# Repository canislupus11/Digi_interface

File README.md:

<div align="center">
<br>

</div>

# Uniwersalny Interfejs Radiowy / Universal Radio Interface

> Kraków, 31 sierpnia 2026 | Hackerspace Kraków  
> Licencja / License: [CC BY-NC-SA](https://creativecommons.org/licenses/by-nc-sa/4.0/)

---

##  Polski (English below)

### Opis projektu

Uniwersalny interfejs radiowy to otwarto-sprzętowy projekt płytki PCB, której celem jest stworzenie jak najbardziej elastycznego interfejsu do **emisji cyfrowych** oraz **zdalnej kontroli urządzeń radiowych (TRX)**. Interfejs zaprojektowano z myślą o kompatybilności z możliwie największą liczbą modeli i producentów transceiverów.

### Główne założenia

- **Uniwersalność** – współpraca z szeroką gamą modeli TRX różnych producentów
- **Minimalizacja okablowania** – w skrajnym przypadku wystarczy kabel USB i kabel sygnałowy do radia
- **Pełna separacja galwaniczna** – izolacja zaraz za gniazdem USB chroni sprzęt przed przepięciami i biegającym RF

### Moduły

| # | Moduł | Chip |
|---|-------|------|
| 1 | HUB USB | **Fe1.1s** |
| 2 | Kodek dźwięku na USB (źródło dla emisji cyfrowych) | **CM108B** |
| 3 | 4-portowy konwerter USB → UART (CAT/CI-V, CW, PTT, FSK) | **CP2105** |
| 4 | Konwerter poziomów RS232/TTL | **MAX232** |
| 5 | Zasilacz (szeroki zakres napięć wejściowych: 7–18 V) | **AMS1117-5.0** |
| 6 | Moduł zworkologii – konfiguracja portów CAT, linii CW, PTT i FSK (w tym z konwerterem poziomów) | – |

### PCB

- Dwustronna płytka w technologii SMD
- Projekt wykonany w **KiCad 9** — pliki schematu, PCB oraz biblioteki footprintów i symboli dostępne w tym repozytorium
- Elementy mają przypisane identyfikatory JLCPCB, dzięki czemu można bezpośrednio zamówić płytkę z usługą montażu SMD (PCBA) — wystarczy wygenerować pliki Gerber, BOM i pliki pick & place z KiCad i wgrać je na stronę JLCPCB
- Katalog `bom/` zawiera interaktywny plik HTNL ułatwiający montaż

### Jak zacząć

1. Sklonuj lub pobierz repozytorium
2. Otwórz `interfejs_digi.kicad_pro` w KiCad 9
3. Przejrzyj schemat (`interfejs_digi.kicad_sch`) i projekt PCB (`interfejs_digi.kicad_pcb`)
4. Wygeneruj pliki Gerber, BOM oraz pick & place z poziomu KiCad
5. Wgraj pliki na stronę [JLCPCB](https://jlcpcb.com) i zamów płytkę z montażem SMD (PCBA) — identyfikatory elementów są już uzupełnione
6. Po otrzymaniu płytki skonfiguruj zworki zgodnie z używanym modelem TRX

### Pinout gniazd RJ45

Interfejs wyprowadza sygnały na dwóch gniazdach RJ45 (HX-RJ45 90 5631-1X1 8P8C).

**RJ1 — gniazdo główne**

| Pin | Sygnał | Opis |
|-----|--------|------|
| 1 | CAT1\_RX | CAT RX/CI-V (port 1) |
| 2 | CAT1\_TX | CAT TX (port 1) |
| 3 | GND\_IN | Masa zasilania |
| 4 | PWR\_IN | Zasilanie 7-18V (wejście) |
| 5 | PTT\_OUT | Wyjście PTT (otwarty dren, tranzystor 2N7002) |
| 6 | GND | Masa sygnałowa |
| 7 | AUDIO\_OUT | Wyjście audio do radia (TX) |
| 8 | AUDIO\_IN | Wejście audio z radia (RX) |

**RJ2 — gniazdo dodatkowe**

| Pin | Sygnał | Opis |
|-----|--------|------|
| 1 | CAT2\_RX | CAT RX (port 2) |
| 2 | CAT2\_TX | CAT TX (port 2) |
| 3 | FSK\_OUT | Wyjście FSK (otwarty dren, tranzystor 2N7002) |
| 4 | 5V_OUT | Wyjście 5V za stabilizatorem |
| 5 | CW\_OUT | Wyjście kluczowania CW (otwarty dren, tranzystor 2N7002) |
| 6 | – | Niepodłączony |
| 7 | – | Niepodłączony |
| 8 | – | Niepodłączony |

Wyjścia PTT, CW i FSK są wyjściami otwartego drenu przez tranzystor MOSFET 2N7002 z diodą LED sygnalizacyjną. Masa obu gniazd jest wspólna (pin 10 złącza RJ45 podłączony do GND).

### Konfiguracja zworkami

Zworki J7–J11 pozwalają elastycznie przypisać sygnały do linii sterujących oraz wybrać poziomy napięć. Każda zworka ma 6 pinów (3 pary), co umożliwia niezależny wybór dla każdej linii.

**J7, J8 — CAT\_1 i CAT\_2**

Pod każdym złączem CAT znajduje się goldpin 2×3 z dwiema klasycznymi zworkami — osobno dla linii RX i TX. Obie zworki ustawia się zawsze w tej samej pozycji. Konfiguracja jest wspólna dla CAT\_1 i CAT\_2:

| Pozycja zworek | Poziom sygnału |
|----------------|----------------|
| obie zworki **w górze** | TTL (5 V) |
| obie zworki **w dole** | RS232 (±12 V) |

**J9 — CW** — wybór źródła sygnału CW spośród linii UART:

| Pozycja zworki | Źródło |
|----------------|--------|
| piny 1–2 | DTR\_1 |
| piny 3–4 | RTS\_1 |
| piny 5–6 | RTS\_2 |

**J10 — PTT** — wybór źródła sygnału PTT:

| Pozycja zworki | Źródło |
|----------------|--------|
| piny 1–2 | DTR\_1 |
| piny 3–4 | RTS\_1 |
| piny 5–6 | RTS\_2 |

**J11 — FSK** — wybór źródła sygnału FSK:

| Pozycja zworki | Źródło |
|----------------|--------|
| piny 1–2 | DTR\_2 |
| piny 3–4 | RTS\_2 |
| piny 5–6 | RTS\_1 |

**J2 — CI-V** — gniazdo CI-V (Icom). Po włożeniu zworki sygnał CAT1\_TX\_TTL jest zwrotnie podłączony przez diodę D5 (1N5819WS) do CAT1\_RX\_TTL, realizując magistralę jednolinową wymaganą przez protokół CI-V.

**LDO\_BYPASS** — lutowana zworka (solder jumper) bypasująca stabilizator napięcia (AMS1117-5.0). Jeśli układ jest zasilany napięciem **5 V** zamiast standardowych 7–18 V (np. bezpośrednio z zasilacza 5 V przez gniazdo RJ1 pin 4), należy zewrzeć tę zworkę cyną, aby ominąć regulator LDO.

> **Ostrzeżenie:** Po zwarciu zworki LDO\_BYPASS stabilizator napięcia jest całkowicie pomijany. Napięcie zasilające trafia bezpośrednio na układ bez żadnej regulacji. Podanie napięcia wyższego niż 5 V przy zwartej zworce **może trwale uszkodzić układ**. Przed podaniem zasilania upewnij się, że źródło napięcia dostarcza dokładnie 5 V.

### Licencja

Projekt udostępniony na licencji **Creative Commons BY-NC-SA**. Możesz go swobodnie używać, modyfikować i udostępniać pod warunkiem podania autora, zachowania tej samej licencji i braku użytku komercyjnego.

---

##  English

### Project Description

The Universal Radio Interface is an open-hardware PCB project designed to provide a flexible interface for **digital mode operations** and **remote control of radio transceivers (TRX)**. The board is designed to be compatible with as many TRX models and manufacturers as possible.

### Design Goals

- **Universality** – works with a wide range of TRX models from various manufacturers
- **Minimal cabling** – in the simplest setup only a USB cable and radio signal cable needed
- **Full galvanic isolation** – isolation placed immediately after the USB connector protects equipment from voltage spikes and stray RF

### Modules

| # | Module | Chip |
|---|--------|------|
| 1 | USB Hub | **Fe1.1s** |
| 2 | USB Audio Codec (source for digital modes) | **CM108B** |
| 3 | 4-port USB → UART converter (CAT/CI-V, CW, PTT, FSK) | **CP2105** |
| 4 | RS232/TTL Level Converter | **MAX232** |
| 5 | Power Supply (wide input voltage range: 7–18 V) | **AMS1117-5.0** |
| 6 | Jumper configuration module – configures CAT ports, CW, PTT and FSK lines (including level converter options) | – |

### PCB

- Double-sided SMD board
- Designed in **KiCad 9** — schematic, PCB layout, footprint and symbol libraries all included in this repository
- All components have JLCPCB part IDs assigned, so the board can be ordered with SMD assembly (PCBA) — simply generate Gerber, BOM and pick & place files from KiCad and upload them to JLCPCB
- The `bom/` directory contains an interactive HTML file to assist with assembly.

### Getting Started

1. Clone or download this repository
2. Open `interfejs_digi.kicad_pro` in KiCad 9
3. Review the schematic (`interfejs_digi.kicad_sch`) and PCB layout (`interfejs_digi.kicad_pcb`)
4. Generate Gerber, BOM and pick & place files from KiCad
5. Upload the files to [JLCPCB](https://jlcpcb.com) and order the board with SMD assembly (PCBA) — component IDs are already filled in
6. Once the board arrives, configure the jumpers for your TRX model

### RJ45 Connector Pinout

The interface exposes signals on two RJ45 connectors (HX-RJ45 90 5631-1X1 8P8C). 

**RJ1 — Main connector**

| Pin | Signal | Description |
|-----|--------|-------------|
| 1 | CAT1\_RX | CAT/CI-V receive (port 1) |
| 2 | CAT1\_TX | CAT/CI-V transmit (port 1) |
| 3 | GND\_IN | Power ground |
| 4 | PWR\_IN | 7-18V power input |
| 5 | PTT\_OUT | PTT output (open drain, 2N7002 MOSFET) |
| 6 | GND | Signal ground |
| 7 | AUDIO\_OUT | Audio output to radio (TX) |
| 8 | AUDIO\_IN | Audio input from radio (RX) |

**RJ2 — Secondary connector**

| Pin | Signal | Description |
|-----|--------|-------------|
| 1 | CAT2\_RX | CAT receive (port 2) |
| 2 | CAT2\_TX | CAT transmit (port 2) |
| 3 | FSK\_OUT | FSK output (open drain, 2N7002 MOSFET) |
| 4 | 5V_OUT | 5V output, after LDO |
| 5 | CW\_OUT | CW keying output (open drain, 2N7002 MOSFET) |
| 6 | – | Not connected |
| 7 | – | Not connected |
| 8 | – | Not connected |

PTT, CW and FSK outputs are open-drain via 2N7002 MOSFET transistors, each with a status LED indicator. The ground of both connectors is shared (RJ45 pin 10 tied to GND).

### Jumper Configuration

Jumpers J7–J11 allow flexible assignment of signals to control lines and voltage level selection. Each jumper has 6 pins (3 pairs), enabling independent selection per line.

**J7, J8 — CAT\_1 and CAT\_2**

Below each CAT connector there is a 2×3 pin header with two standard jumpers — one for RX and one for TX. Both jumpers are always set to the same position. The configuration applies equally to CAT\_1 and CAT\_2:

| Jumper position | Signal level |
|-----------------|--------------|
| both jumpers **up** | TTL (5 V) |
| both jumpers **down** | RS232 (±12 V) |

**J9 — CW** — selects the UART line used as the CW source:

| Jumper position | Source |
|-----------------|--------|
| pins 1–2 | DTR\_1 |
| pins 3–4 | RTS\_1 |
| pins 5–6 | RTS\_2 |

**J10 — PTT** — selects the PTT source:

| Jumper position | Source |
|-----------------|--------|
| pins 1–2 | DTR\_1 |
| pins 3–4 | RTS\_1 |
| pins 5–6 | RTS\_2 |

**J11 — FSK** — selects the FSK source:

| Jumper position | Source |
|-----------------|--------|
| pins 1–2 | DTR\_2 |
| pins 3–4 | RTS\_2 |
| pins 5–6 | RTS\_1 |

**J2 — CI-V** — CI-V connector (Icom radios). When a jumper is inserted, CAT1\_TX\_TTL is looped back through diode D5 (1N5819WS) to CAT1\_RX\_TTL, implementing the single-wire bus required by the CI-V protocol.

**LDO\_BYPASS** — solder jumper that bypasses the voltage regulator (AMS1117-5.0). If the board is powered at **5 V** instead of the standard 7–18 V range (e.g. directly from a 5 V supply via RJ1 pin 4), bridge this solder jumper to bypass the LDO regulator.

> **Warning:** When the LDO\_BYPASS solder jumper is bridged, the voltage regulator is completely bypassed. The supply voltage is fed directly to the circuitry with no regulation. Applying more than 5 V with this jumper bridged **can permanently damage the board**. Always verify that your power source provides exactly 5 V before powering on.

### License

This project is released under the **Creative Commons BY-NC-SA** license. You are free to use, modify, and share it as long as you credit the author, keep the same license, and do not use it commercially.

---

*Design by Szymon Reiter / Hackerspace Kraków*

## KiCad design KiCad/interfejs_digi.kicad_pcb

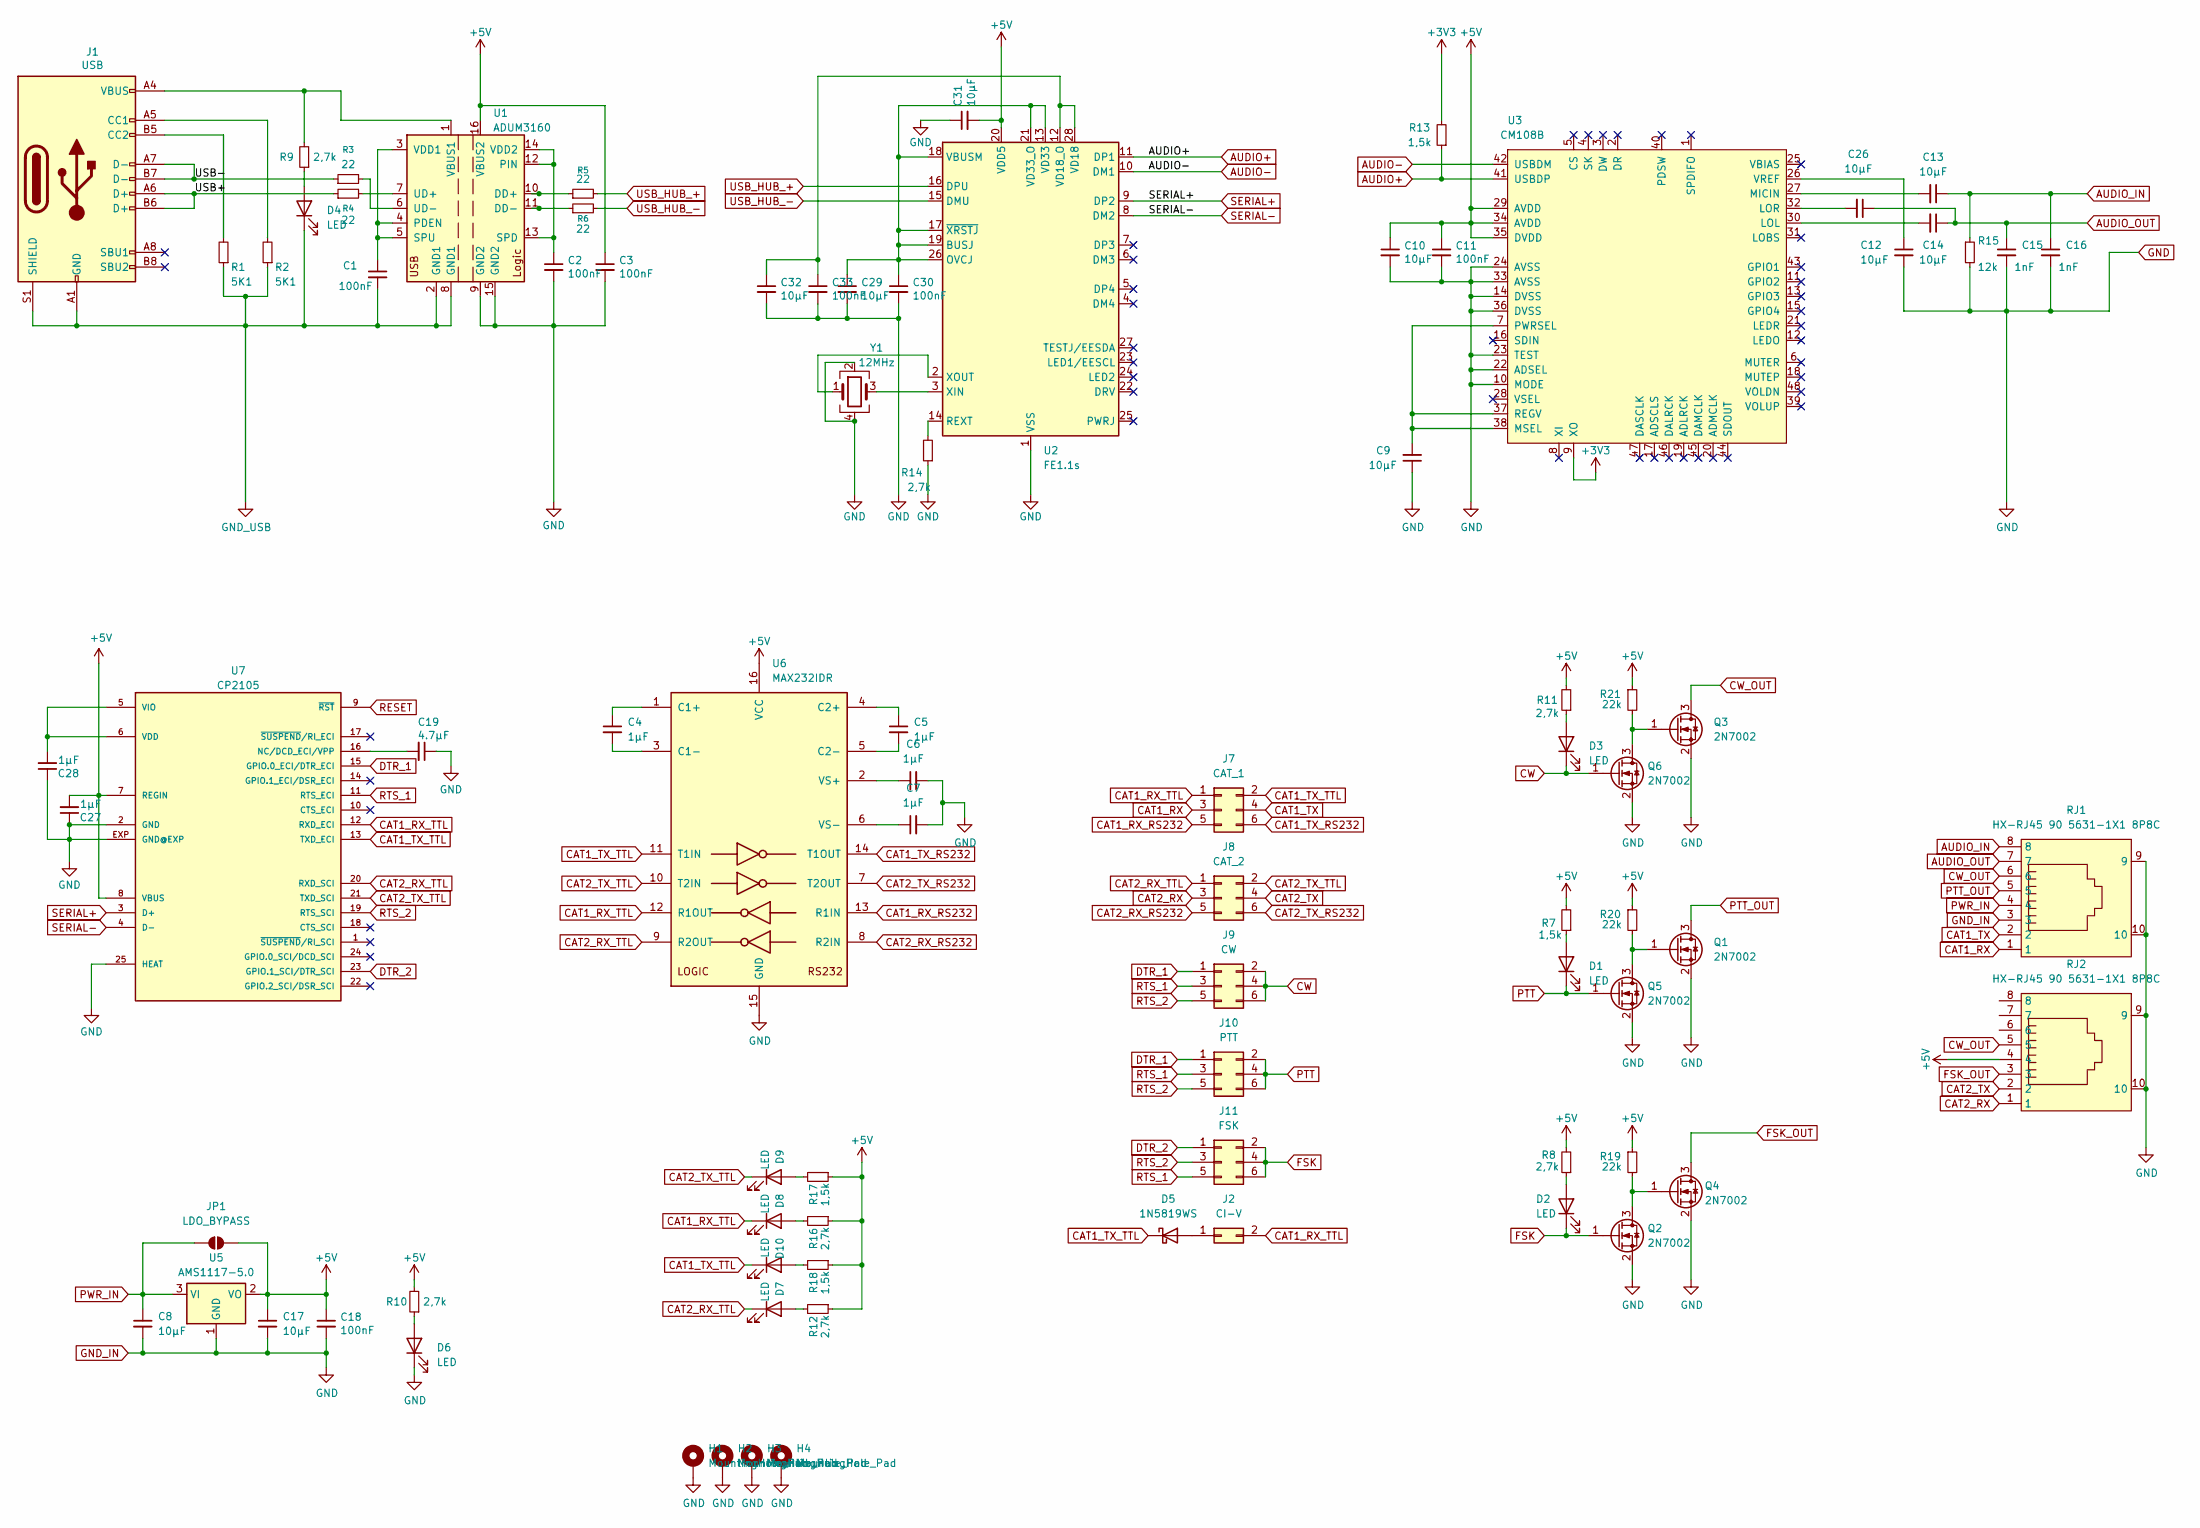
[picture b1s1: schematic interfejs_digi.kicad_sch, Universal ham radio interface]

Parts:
C1, C2, C3, C11, C18, C30, C33: 100nF; C_0603_1608Metric; LCSC C14663
C4, C5, C6, C7, C27, C28: 1µF; C_0603_1608Metric; LCSC C15849
C8, C9, C10, C12, C13, C14, C17, C26, C29, C31, C32: 10µF; C_0603_1608Metric; LCSC C19702
C15, C16: 1nF; C_0603_1608Metric; LCSC C1588
C19: 4.7µF; C_0603_1608Metric; LCSC C19666
D1, D9, D10: LED; LED_0805_2012Metric; LCSC C84256
D2, D3, D4, D6, D7, D8: LED; LED_0805_2012Metric; LCSC C2297
D5: 1N5819WS; D_SOD-323; LCSC C191023
H1, H2, H3, H4: MountingHole_Pad; MountingHole_3.2mm_M3_Pad_Via
J1: USB; USB_C_Receptacle_HRO_TYPE-C-31-M-12; LCSC C393939
J2: CI-V; PinHeader_1x02_P2.54mm_Vertical; LCSC C41430884
J7: CAT_1; PinHeader_2x03_P2.54mm_Vertical; LCSC C65114
J8: CAT_2; PinHeader_2x03_P2.54mm_Vertical; LCSC C65114
J9: CW; PinHeader_2x03_P2.54mm_Vertical; LCSC C65114
J10: PTT; PinHeader_2x03_P2.54mm_Vertical; LCSC C65114
J11: FSK; PinHeader_2x03_P2.54mm_Vertical; LCSC C65114
JP1: LDO_BYPASS; SolderJumper-2_P1.3mm_Open_RoundedPad1.0x1.5mm
Q1, Q2, Q3, Q4, Q5, Q6: 2N7002; SOT-23; LCSC C8545
R1, R2: 5K1; R_0603_1608Metric; LCSC C23186
R3, R4, R5, R6: 22; R_0603_1608Metric; LCSC C23345
R7, R13, R17, R18: 1,5k; R_0603_1608Metric; LCSC C22843
R8, R9, R10, R11, R12, R14, R16: 2,7k; R_0603_1608Metric; LCSC C13167
R15: 12k; R_0603_1608Metric; LCSC C22790
R19, R20, R21: 22k; R_0603_1608Metric; LCSC C31850
RJ1, RJ2: HX-RJ45 90 5631-1X1 8P8C; RJ456-TH_HX-RJ45-90-5631-1X1-8P8C; LCSC C25168869
U1: ADUM3160; SOIC-16W_7.5x10.3mm_P1.27mm; LCSC C284149
U2: FE1.1s; SSOP-28_3.9x9.9mm_P0.635mm; LCSC C9359
U3: CM108B; LQFP-48_7x7mm_P0.5mm; LCSC C371347
U5: AMS1117-5.0; SOT-223-3_TabPin2; LCSC C6187
U6: MAX232IDR; SOIC-16_3.9x9.9mm_P1.27mm; JLCPCB# C59824
U7: CP2105; QFN-24_L4.0-W4.0-P0.50-BL-EP2.6; LCSC C109102
Y1: 12MHz; Crystal_SMD_3225-4Pin_3.2x2.5mm; LCSC C9002

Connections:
+3V3: R13.2, U3.9 (XO)
+5V: C3.1, C10.1, C11.1, C17.1, C18.1, C27.2, C31.2, JP1.2 (B), R7.2, R8.2, R10.2, R11.2, R12.1, R16.1, R17.1, R18.1, R19.1, R20.1, R21.1, RJ2.4, U1.16 (VBUS2), U2.20 (VDD5), U3.29 (AVDD), U3.34 (AVDD), U3.35 (DVDD), U5.2 (VO), U6.16 (VCC), U7.7 (REGIN), U7.8 (VBUS)
/USB+: J1.A6 (D+), J1.B6 (D+), R4.1
/USB-: J1.A7 (D-), J1.B7 (D-), R3.1
AUDIO+: R13.1, U2.11 (DP1), U3.41 (USBDP)
AUDIO-: U2.10 (DM1), U3.42 (USBDM)
AUDIO_IN: C13.1, C16.1, R15.1, RJ1.8
AUDIO_OUT: C14.1, C15.1, C26.1, RJ1.7
CAT1_RX: J7.3, RJ1.1
CAT1_RX_RS232: J7.5, U6.13 (R1IN)
CAT1_RX_TTL: D8.1 (K), J2.2, J7.1, U6.12 (R1OUT), U7.12 (RXD_ECI)
CAT1_TX: J7.4, RJ1.2
CAT1_TX_RS232: J7.6, U6.14 (T1OUT)
CAT1_TX_TTL: D5.1 (K), D10.1 (K), J7.2, U6.11 (T1IN), U7.13 (TXD_ECI)
CAT2_RX: J8.3, RJ2.1
CAT2_RX_RS232: J8.5, U6.8 (R2IN)
CAT2_RX_TTL: D7.1 (K), J8.1, U6.9 (R2OUT), U7.20 (RXD_SCI)
CAT2_TX: J8.4, RJ2.2
CAT2_TX_RS232: J8.6, U6.7 (T2OUT)
CAT2_TX_TTL: D9.1 (K), J8.2, U6.10 (T2IN), U7.21 (TXD_SCI)
CW: D3.1 (K), J9.2, J9.4, J9.6, Q6.1 (G)
CW_OUT: Q3.3 (D), RJ1.6, RJ2.5
DTR_1: J9.1, J10.1, U7.15 (GPIO.0_ECI/DTR_ECI)
DTR_2: J11.1, U7.23 (GPIO.1_SCI/DTR_SCI)
FSK: D2.1 (K), J11.2, J11.4, J11.6, Q2.1 (G)
FSK_OUT: Q4.3 (D), RJ2.3
GND: C2.2, C3.2, C6.2, C7.2, C8.2, C9.1, C10.2, C11.2, C12.2, C15.2, C16.2, C17.2, C18.2, C19.1, C27.1, C28.1, C29.2, C30.2, C31.1, C32.2, C33.2, D6.1 (K), H1.1, H2.1, H3.1, H4.1, Q1.2 (S), Q2.2 (S), Q3.2 (S), Q4.2 (S), Q5.2 (S), Q6.2 (S), R14.1, R15.2, RJ1.3, RJ1.9, RJ1.10, RJ2.9, RJ2.10, U1.9 (GND2), U1.15 (GND2), U2.1 (VSS), U3.10 (MODE), U3.14 (DVSS), U3.22 (ADSEL), U3.23 (TEST), U3.24 (AVSS), U3.33 (AVSS), U3.36 (DVSS), U5.1 (GND), U6.15 (GND), U7.2 (GND), U7.25 (HEAT), U7.EXP (GND@EXP), Y1.2, Y1.4
GND_USB: C1.2, D4.1 (K), J1.A1 (GND), J1.A12 (GND), J1.B1 (GND), J1.B12 (GND), J1.S1 (SHIELD), R1.1, R2.1, U1.2 (GND1), U1.8 (GND1)
unnamed: D1.2 (A), R7.1
unnamed: D2.2 (A), R8.1
unnamed: D3.2 (A), R11.1
unnamed: D4.2 (A), R9.1
unnamed: D5.2 (A), J2.1
unnamed: D6.2 (A), R10.1
unnamed: D7.2 (A), R12.2
unnamed: D8.2 (A), R16.2
unnamed: D9.2 (A), R17.2
unnamed: D10.2 (A), R18.2
unnamed: J1.A5 (CC1), R2.2
unnamed: J1.B5 (CC2), R1.2
unnamed: Q1.1 (G), Q5.3 (D), R20.2
unnamed: Q2.3 (D), Q4.1 (G), R19.2
unnamed: Q3.1 (G), Q6.3 (D), R21.2
unnamed: R5.1, U1.10 (DD+)
unnamed: R6.1, U1.11 (DD-)
unnamed: C1.1, U1.3 (VDD1), U1.4 (PDEN), U1.5 (SPU)
unnamed: C2.1, U1.12 (PIN), U1.13 (SPD), U1.14 (VDD2)
unnamed: R4.2, U1.7 (UD+)
unnamed: R3.2, U1.6 (UD-)
unnamed: J1.A4 (VBUS), J1.A9 (VBUS), J1.B4 (VBUS), J1.B9 (VBUS), R9.2, U1.1 (VBUS1)
unnamed: C29.1, C30.1, U2.13 (VD33), U2.17 (~XRSTJ), U2.18 (VBUSM), U2.19 (BUSJ), U2.21 (VD33_O), U2.26 (OVCJ)
unnamed: R14.2, U2.14 (REXT)
unnamed: C32.1, C33.1, U2.12 (VD18_O), U2.28 (VD18)
unnamed: U2.3 (XIN), Y1.3
unnamed: U2.2 (XOUT), Y1.1
unnamed: C14.2, U3.30 (LOL)
unnamed: C26.2, U3.32 (LOR)
unnamed: C13.2, U3.27 (MICIN)
unnamed: C9.2, U3.7 (PWRSEL), U3.37 (REGV), U3.38 (MSEL)
unnamed: C12.1, U3.26 (VREF)
unnamed: C4.1, U6.1 (C1+)
unnamed: C4.2, U6.3 (C1-)
unnamed: C5.1, U6.4 (C2+)
unnamed: C5.2, U6.5 (C2-)
unnamed: C6.1, U6.2 (VS+)
unnamed: C7.1, U6.6 (VS-)
unnamed: C19.2, U7.16 (NC/DCD_ECI/VPP)
unnamed: C28.2, U7.5 (VIO), U7.6 (VDD)
PTT: D1.1 (K), J10.2, J10.4, J10.6, Q5.1 (G)
PTT_OUT: Q1.3 (D), RJ1.5
PWR_IN: C8.1, JP1.1 (A), RJ1.4, U5.3 (VI)
RESET: U7.9 (~RST)
RTS_1: J9.3, J10.3, J11.5, U7.11 (RTS_ECI)
RTS_2: J9.5, J10.5, J11.3, U7.19 (RTS_SCI)
SERIAL+: U2.9 (DP2), U7.3 (D+)
SERIAL-: U2.8 (DM2), U7.4 (D-)
USB_HUB_+: R5.2, U2.16 (DPU)
USB_HUB_-: R6.2, U2.15 (DMU)

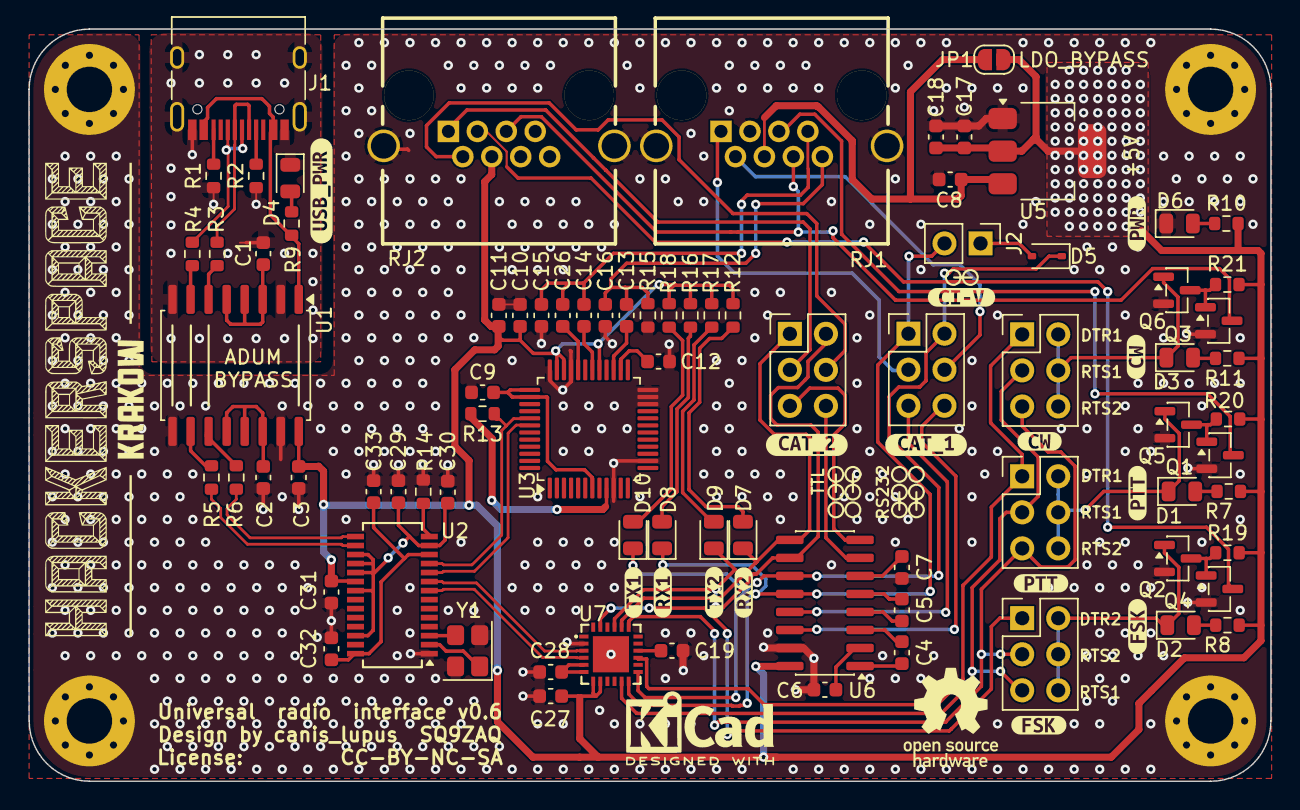
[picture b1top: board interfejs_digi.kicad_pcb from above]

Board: 2 copper layers, 87.5 x 53.0 mm, 100 parts (0 on the bottom side), 77 nets.

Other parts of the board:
kibuzzard-69B08B73, kibuzzard-69B08B73#2: G***; kibuzzard-69B08B73
kibuzzard-69B08B92, kibuzzard-69B08B92#2: G***; kibuzzard-69B08B92
kibuzzard-69B08BB3, kibuzzard-69B08BB3#2: G***; kibuzzard-69B08BB3
kibuzzard-69B08C88: G***; kibuzzard-69B08C88
kibuzzard-69B08CED: G***; kibuzzard-69B08CED
kibuzzard-69B08D19: G***; kibuzzard-69B08D19
kibuzzard-69B08EE7: G***; kibuzzard-69B08EE7
kibuzzard-69B0953C: G***; kibuzzard-69B0953C
kibuzzard-69E7E9BF: G***; kibuzzard-69E7E9BF
kibuzzard-69E7EA0C: G***; kibuzzard-69E7EA0C
kibuzzard-69E7EA01: G***; kibuzzard-69E7EA01
kibuzzard-69E7EA14: G***; kibuzzard-69E7EA14

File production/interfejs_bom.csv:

Designator,Footprint,Quantity,Value,LCSC Part #
"C1, C11, C18, C2, C3, C30, C33",0603,7,100nF,C14663
"C10, C12, C13, C14, C17, C26, C29, C31, C32, C8, C9",0603,11,10µF,C19702
"C15, C16",0603,2,1nF,C1588
C19,0603,1,4.7µF,C19666
"C27, C28, C4, C5, C6, C7",0603,6,1µF,C15849
D1,0805,1,LED, C84256
"D10, D2, D3, D4, D6, D7, D8, D9",0805,8,LED,C2297
D5,D_SOD-323,1,1N5819WS,C191023
J1,USB_C_Receptacle_HRO_TYPE-C-31-M-12,1,USB,C393939
J10,PinHeader_2x03_P2.54mm_Vertical,1,PTT,C65114
J11,PinHeader_2x03_P2.54mm_Vertical,1,FSK,C65114
J2,PinHeader_1x02_P2.54mm_Vertical,1,CI-V,C41430884
J7,PinHeader_2x03_P2.54mm_Vertical,1,CAT_1,C65114
J8,PinHeader_2x03_P2.54mm_Vertical,1,CAT_2,C65114
J9,PinHeader_2x03_P2.54mm_Vertical,1,CW,C65114
"Q1, Q2, Q3",SOT-23,3,2N7002,C8545
"R1, R2",0603,2,5K1,C23186
"R10, R11, R12, R14, R16, R17, R18, R8, R9",0603,9,"2,7k",C13167
"R13, R7",0603,2,"1,5k",C22843
R15,0603,1,12k,C22790
"R3, R4, R5, R6",0603,4,22,C23345
"RJ1, RJ2",RJ456-TH_HX-RJ45-90-5631-1X1-8P8C,2,HX-RJ45 90 5631-1X1 8P8C,C25168869
U1,SOIC-16W_7.5x10.3mm_P1.27mm,1,ADUM4160,C57791
U2,SSOP-28_3.9x9.9mm_P0.635mm,1,FE1.1s,C9359
U3,LQFP-48_7x7mm_P0.5mm,1,CM108B,C371347
U5,SOT-223-3_TabPin2,1,AMS1117-5.0, C6187
U6,SOIC-16_3.9x9.9mm_P1.27mm,1,MAX232IDR,
U7,QFN-24_L4.0-W4.0-P0.50-BL-EP2.6,1,CP2105,C109102
Y1,Crystal_SMD_3225-4Pin_3.2x2.5mm,1,12MHz,C9002

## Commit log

2026-04-25 init commit
2026-04-25 poprawki
2026-04-25 ignore production
2026-04-28 update1
2026-05-02 zmiana wyjscia starujacego
